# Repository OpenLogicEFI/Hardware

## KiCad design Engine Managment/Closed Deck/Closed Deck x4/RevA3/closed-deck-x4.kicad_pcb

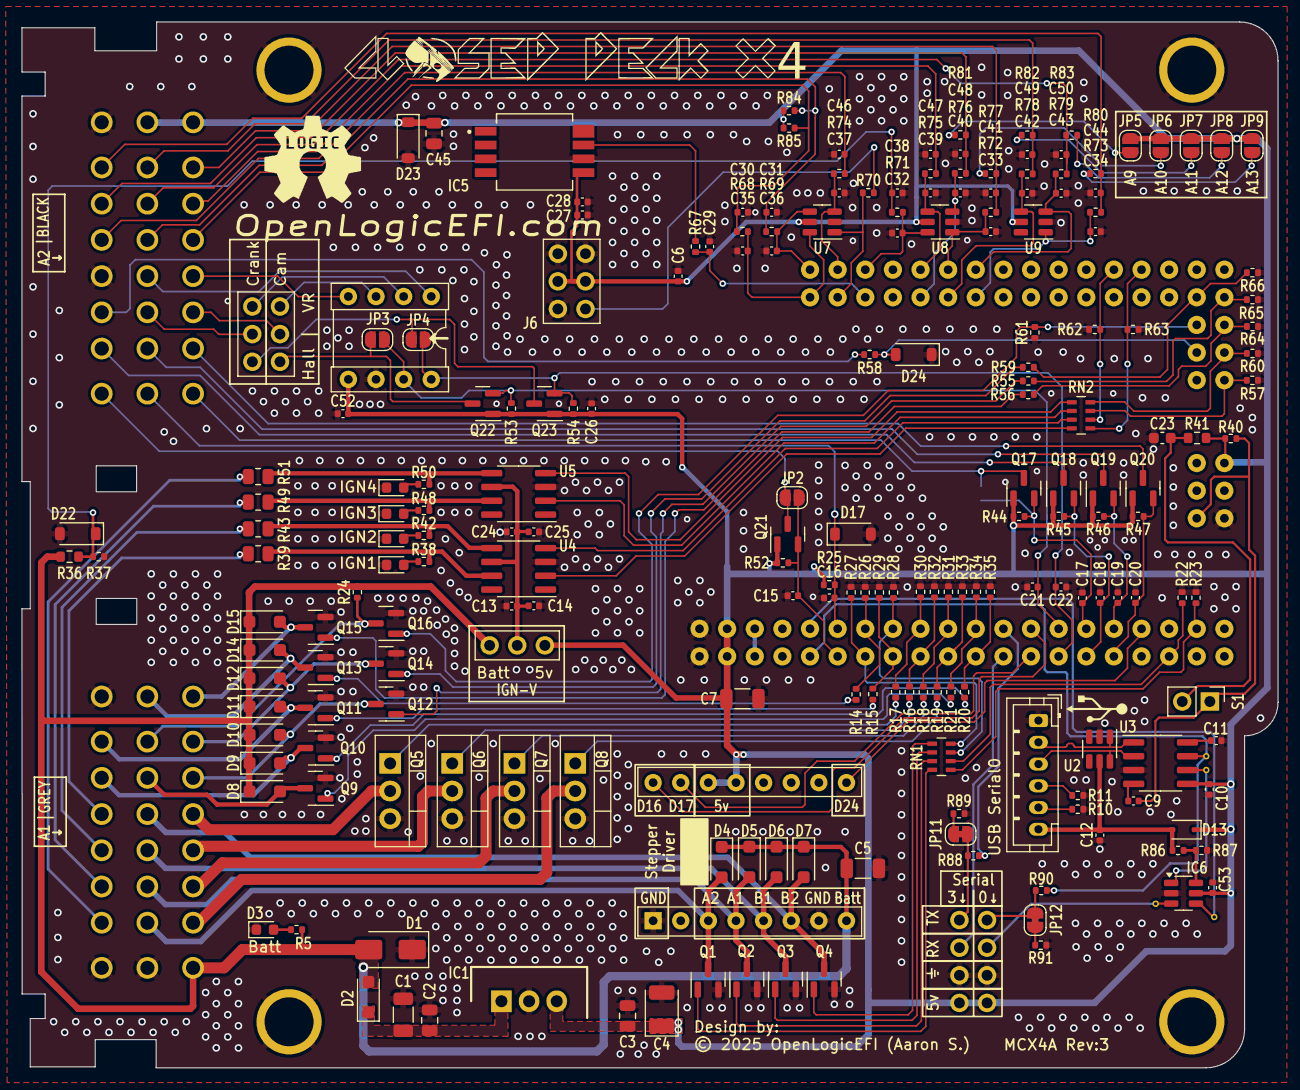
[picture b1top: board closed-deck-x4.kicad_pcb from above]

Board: 2 copper layers, 115.5 x 96.2 mm, 220 parts (1 on the bottom side), 149 nets.

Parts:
A1: GREY; Delphi_Sicma_24_Grey
A2: BLACK; Delphi_Sicma_24_Black
C1, C5, C7: 10uF; C_1206_3216Metric
C2: 330nF; C_0805_2012Metric
C3, C45: 100nF; C_0805_2012Metric
C4: 100uF; CP_EIA-3528-15_AVX-H
C6, C9, C10, C11, C12, C13, C15, C21, C24, C26, C28, C29, C35, C36, C38, C41, C44, C46, C47, C48, C49, C50, C52, C53: 100nF; C_0402_1005Metric
C14, C25, C27: 1u; C_0402_1005Metric
C16, C30, C31, C32, C33, C34, C37, C39, C40, C42, C43: 220nF; C_0402_1005Metric
C17, C18, C19, C20, C22: 10nF; C_0402_1005Metric
C23: 10uF; C_0603_1608Metric
D1: SMAJ18CA; D_SMA
D2, D4, D5, D6, D7, D8, D9, D10, D11, D12, D14, D15: DSK210; D_SOD-123F
D3, D16, D18, D20, D21: LED; LED_0603_1608Metric
D13: 1N5819WS; D_SOD-323
D17, D22, D23, D24: MMSZ5232B; D_SOD-123
H1, H2, H3, H4: MountingHole_Pad; MountingHole_3.5mm_Pad
IC1: 7805; TO-220-SmallHeatSink
IC2: Breakout DRV8825; DVR8825-Labeled-Front
IC5: KP234; KP234-Handsoldering
IC6: 74LVC1G157GV,125; TSOT-23-6
J2: Serial; 2x04-2.54mm-Serial-withSilk
J3: USB-S0; JST_PH_B6B-PH-K_1x06_P2.00mm_Vertical
J4: Input Jumper; PinHeader2x03_Jumper
J5: VR Conditioner; Socket_VRConditioner_Corrected
J6: Map Sensor Socket; PinSocket 2x03
JP1: IGN-V; 1x03-Proto
JP2, JP3, JP4, JP10: FET Bypass; SolderJumper-2_P1.3mm_Open_RoundedPad1.0x1.5mm
JP5, JP6, JP7, JP8, JP9: SolderJumper_2_Open; SolderJumper-2_P1.3mm_Open_RoundedPad1.0x1.5mm
JP11, JP12: Divider Disable; SolderJumper-2_P1.3mm_Bridged_RoundedPad1.0x1.5mm
Q1, Q2, Q3, Q4, Q9, Q10, Q11, Q12, Q13, Q14, Q15, Q16, Q17, Q18, Q19, Q20, Q21, Q22, Q23: AO3400A; SOT-23
Q5, Q6, Q7, Q8: STP75N04Z; TO-220-3_Vertical
R5, R38, R42, R48, R50, R89, R91: 2k; R_0402_1005Metric
R10, R11: 5.1k; R_0402_1005Metric
R14, R15, R20, R21, R55, R56, R59, R68, R69, R70, R71, R72, R73, R74, R75, R76, R78, R79, R86: 470r; R_0402_1005Metric
R16, R17, R18, R19, R37, R44, R45, R46, R47, R52, R53, R54, R58, R88, R90: 1k; R_0402_1005Metric
R22, R23, R26, R27, R28, R29, R34, R35, R64, R65, R66: 100k; R_0402_1005Metric
R24, R40, R87: 10k; R_0402_1005Metric
R25: 2.2k; R_0402_1005Metric
R30, R31, R32, R33, R57, R60, R61, R62, R63: 100K; R_0402_1005Metric
R36: 3.9k; R_0603_1608Metric
R39, R43, R49, R51: 10r; R_0805_2012Metric
R41: 120r; R_0603_1608Metric
R67: 51k; R_0402_1005Metric
R77, R80, R81, R82, R83, R84, R85: 2.49k; R_0402_1005Metric
RN1, RN2: 1k; R_Array_Concave_4x0603
S1: Reset Control; PinHeader_1x02_P2.54mm_Vertical
TP4, TP5, TP8, TP9: TestPoint; TestPoint_THT_D0.6mm_Drill0.3mm
U2, U7, U8, U9: SRV05-4-P-T7; SOT-23-6
U3: CH340N; SOIC-8_3.9x4.9mm_P1.27mm
U4, U5: COS4427; SOIC-8_3.9x4.9mm_P1.27mm
U6: MEGA_PRO_EMBED_CH340G_{slash}_ATMEGA2560; Arduino_Mega_Mini_2560_SmallCrtYd_NoVin

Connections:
+3.3V: U6.3V3_1 (3V3), U6.3V3_2 (3V3)
+5V: A2.A8, A2.B8, C3.1, C4.1, C6.2, C7.1, C10.1, C26.2, C27.1, C28.1, C45.1, C52.2, C53.2, D13.1 (K), D23.1 (K), IC1.3 (OUT), IC2.13 (~RST), IC2.14 (~SLP), IC5.5 (VDD), IC6.5 (VCC), J2.1, J2.2, J5.5, J6.3, J6.4, JP1.3 (B), JP5.1 (A), JP6.1 (A), JP7.1 (A), JP8.1 (A), JP9.1 (A), Q17.1 (G), Q18.1 (G), Q19.1 (G), Q20.1 (G), Q21.1 (G), Q22.1 (G), Q23.1 (G), R25.1, R40.1, R41.2, R44.1, R45.1, R46.1, R47.1, R52.1, R53.1, R54.1, R84.1, R85.1, U3.5 (VCC), U6.5V_1 (5V), U6.5V_2 (5V), U6.5V_3 (5V), U7.5 (REF), U8.5 (REF), U9.5 (REF)
+BATT: A1.A1, C5.1, D1.2 (A2), D2.2 (A), D4.1 (K), D5.1 (K), D6.1 (K), D7.1 (K), D8.1 (K), D9.1 (K), D10.1 (K), D11.1 (K), D12.1 (K), D14.1 (K), D15.1 (K), IC2.8 (VMOT), JP1.1 (A), R5.2, R24.1, R36.2
A9: A2.C6, C48.1, R76.2, R81.2
A10: A2.A7, C41.1, R72.2, R77.2
A11: A2.B7, C49.1, R78.2, R82.2
A12: A2.B6, C50.1, R79.2, R83.2
A13: A2.C7, C44.1, R73.2, R80.2
BOOST: A1.C7, D11.2 (A), Q11.3 (D)
BaroIn: IC5.7 (VOUT), R67.1
CH340-RX0: IC6.1 (I1), TP4.1, U3.6 (RXD)
CLT: A2.A5, C35.1, R68.2, R85.2
Cam2: A2.C1, JP2.1 (A), Q21.3 (D)
Cam-Direct: J4.b3, JP3.1 (A), Q22.3 (D)
Cam-In: A2.A3, J4.b2
Clutch: A2.C3, R58.1
Crank-Direct: J4.a3, JP4.1 (A), Q23.3 (D)
Crank-In: A2.B3, J4.a2
D12-OUT: A1.B6, D8.2 (A), Q9.3 (D)
D13-OUT: A1.C6, D9.2 (A), Q10.3 (D)
D21-IN: A2.C2, Q18.3 (D)
D22-IN: A2.B2, Q19.3 (D)
D23-IN: A2.A2, Q20.3 (D)
D27-OUT: A1.B3, D5.2 (A), IC2.4 (A1), Q2.3 (D)
D28-OUT: A1.B2, D4.2 (A), IC2.3 (A2), Q1.3 (D)
D+: J3.2, U2.1 (I/O_1), U3.1 (UD+)
D-: J3.3, U2.6 (I/O_4), U3.2 (UD-)
Fan: A1.A6, D10.2 (A), Q12.3 (D)
Flex: A2.B1, C16.1, D17.1 (A1), R25.2, U6.D2
Fuel-Pump: A1.A7, D12.2 (A), Q14.3 (D)
GND: A1.B1, A1.C1, A1.C8, A2.C4, A2.C8, C1.2, C2.2, C3.2, C4.2, C5.2, C6.1, C7.2, C10.2, C11.2, C12.2, C13.2, C14.2, C15.1, C16.2, C17.2, C18.2, C19.2, C20.2, C21.1, C22.1, C23.2, C24.2, C25.2, C26.1, C27.2, C28.2, C29.2, C30.2, C31.2, C32.2, C33.2, C34.2, C35.2, C36.2, C37.2, C38.2, C39.2, C40.2, C41.2, C42.2, C43.2, C44.2, C45.2, C46.2, C47.2, C48.2, C49.2, C50.2, C52.1, C53.1, D1.1 (A1), D3.1 (K), D16.1 (K), D17.2 (A2), D18.1 (K), D20.1 (K), D21.1 (K), D22.2 (A2), D23.2 (A), D24.1 (A1), H1.1, H2.1, H3.1, H4.1, IC1.2 (GND), IC2.1 (GND), IC2.7 (GND), IC5.6 (GND), IC6.2 (GND), J2.3, J2.4, J3.1, J5.6, J6.1, J6.5, J6.6, Q1.2 (S), Q2.2 (S), Q3.2 (S), Q4.2 (S), Q5.3 (S), Q6.3 (S), Q7.3 (S), Q8.3 (S), Q9.2 (S), Q10.2 (S), Q11.2 (S), Q12.2 (S), Q13.2 (S), Q14.2 (S), Q15.2 (S), Q16.2 (S), R10.1, R11.2, R22.1, R23.1, R26.1, R27.1, R28.1, R29.1, R30.1, R31.1, R32.1, R33.1, R34.1, R35.1, R37.1, R57.2, R60.2, R61.2, R62.1, R63.2, R64.1, R65.1, R66.1, R87.1, R89.2, R91.2, U2.2 (GND), U3.3 (GND), U4.3 (GND), U5.3 (GND), U6.GND_1 (GND), U6.GND_2 (GND), U6.GND_3 (GND), U7.2 (GND), U8.2 (GND), U9.2 (GND)
IAT: A2.B5, C36.1, R69.2, R84.2
IDLE1: A1.B5, D7.2 (A), IC2.6 (B2), Q4.3 (D)
IDLE2: A1.B4, D6.2 (A), IC2.5 (B1), Q3.3 (D)
IGN1: A1.C5, R39.2
IGN2: A1.C4, R43.2
IGN3: A1.C3, R49.2
IGN4: A1.C2, R51.2
INJ1: A1.A5, Q5.2 (D)
INJ2: A1.A4, Q6.2 (D)
INJ3: A1.A3, Q7.2 (D)
INJ4: A1.A2, Q8.2 (D)
MC-A0: C31.1, R69.1, U6.A0, U7.4 (I/O_3)
MC-A1: C30.1, R68.1, U6.A1, U7.6 (I/O_4)
MC-A2: C37.1, R74.1, U6.A2, U7.3 (I/O_2)
MC-A3: R70.1, U6.A3, U7.1 (I/O_1)
MC-A4: C32.1, R71.1, U6.A4, U8.6 (I/O_4)
MC-A5: C29.1, R67.2, U6.A5
MC-A8: C39.1, R75.1, U6.A8, U8.4 (I/O_3)
MC-A9: C40.1, R76.1, U6.A9, U8.3 (I/O_2)
MC-A10: C33.1, R72.1, U6.A10, U8.1 (I/O_1)
MC-A11: C42.1, R78.1, U6.A11, U9.4 (I/O_3)
MC-A12: C43.1, R79.1, U6.A12, U9.3 (I/O_2)
MC-A13: C34.1, R73.1, U6.A13, U9.1 (I/O_1)
MC-D0-RX0: IC6.4 (Y), TP8.1, U6.RX
MC-D1-TX0: R90.1, TP5.1, U3.7 (TXD), U6.TX
MC-D3: C15.2, JP2.2 (B), Q21.2 (S), R52.2, U6.D3
MC-D4: R14.1, R26.2, U6.D4
MC-D5: R27.2, RN1.8 (R1.2), U6.D5
MC-D6: R28.2, RN1.7 (R2.2), U6.D6
MC-D7: R15.1, R29.2, U6.D7
MC-D8: R17.1, R30.2, U6.D8
MC-D9: R16.1, R32.2, U6.D9
MC-D10: R18.1, R31.2, U6.D10
MC-D11: R19.1, R33.2, U6.D11
MC-D12: R21.1, R34.2, U6.D12
MC-D13: R20.1, R35.2, U6.D13
MC-D14-TX3: R88.1, U6.D14
MC-D15-RX3: J2.5, U6.D15
MC-D16: IC2.16 (DIR), U6.D16
MC-D17: IC2.15 (STEP), U6.D17
MC-D18: C21.2, J5.7, JP3.2 (B), Q22.2 (S), R53.2, U6.D18
MC-D19: C22.2, J5.8, JP4.2 (B), Q23.2 (S), R54.2, U6.D19
MC-D20: C17.1, JP10.2 (B), Q17.2 (S), R44.2, U6.D20
MC-D21: C18.1, Q18.2 (S), R45.2, U6.D21
MC-D22: C19.1, Q19.2 (S), R46.2, U6.D22
MC-D23: C20.1, Q20.2 (S), R47.2, U6.D23
MC-D24: IC2.9 (~EN), U6.D24
MC-D27: R22.2, RN1.6 (R3.2), U6.D27
MC-D28: R23.2, RN1.5 (R4.2), U6.D28
MC-D38: R62.2, RN2.6 (R3.2), U6.D38
MC-D40: R63.1, RN2.5 (R4.2), U6.D40
MC-D45: R59.1, R66.2, U6.D45
MC-D47: R55.1, R65.2, U6.D47
MC-D48: R56.1, R64.2, U6.D48
MC-D49: Q16.1 (G), R61.1, U6.D49
MC-D50: R60.1, RN2.8 (R1.2), U6.D50
MC-D51: D24.2 (A2), R58.2, U6.D51
MC-D52: R57.1, RN2.7 (R2.2), U6.D52
MC-RESET: C9.2, R40.2, S1.1, U6.RESET
MapIn: J6.2, R70.2
unnamed: C1.1, C2.1, D2.1 (K), IC1.1 (IN)
unnamed: D3.2 (A), R5.1
unnamed: D16.2 (A), R38.1
unnamed: D18.2 (A), R42.1
unnamed: D20.2 (A), R48.1
unnamed: D21.2 (A), R50.1
unnamed: C38.1, D22.1 (A1), R36.1, R37.2, R71.2
unnamed: IC6.6 (S), R86.1, R87.2
unnamed: J2.7, JP11.2 (B), R88.2
unnamed: J2.8, JP12.1 (A), R90.2
unnamed: J3.4, R11.1
unnamed: J3.5, R10.2
unnamed: C13.1, C14.1, C24.1, C25.1, JP1.2 (C), U4.6 (V+), U5.6 (V+)
unnamed: JP5.2 (B), R81.1
unnamed: JP6.2 (B), R77.1
unnamed: JP7.2 (B), R82.1
unnamed: JP8.2 (B), R83.1
unnamed: JP9.2 (B), R80.1
unnamed: JP11.1 (A), R89.1
unnamed: JP12.2 (B), R91.1
unnamed: Q1.1 (G), RN1.4 (R4.1)
unnamed: Q2.1 (G), RN1.3 (R3.1)
unnamed: Q3.1 (G), RN1.2 (R2.1)
unnamed: Q4.1 (G), RN1.1 (R1.1)
unnamed: Q5.1 (G), R17.2
unnamed: Q6.1 (G), R16.2
unnamed: Q7.1 (G), R18.2
unnamed: Q8.1 (G), R19.2
unnamed: Q9.1 (G), R21.2
unnamed: Q10.1 (G), R20.2
unnamed: Q11.1 (G), R15.2
unnamed: Q12.1 (G), R55.2
unnamed: Q13.1 (G), R14.2
unnamed: Q14.1 (G), R59.2
unnamed: Q15.1 (G), R56.2
unnamed: RN2.1 (R1.1), U5.4 (IN_B)
unnamed: RN2.2 (R2.1), U5.2 (IN_A)
unnamed: RN2.3 (R3.1), U4.4 (IN_B)
unnamed: RN2.4 (R4.1), U4.2 (IN_A)
unnamed: C23.1, R41.1, S1.2
unnamed: C11.1, U3.8 (V3)
unnamed: C9.1, U3.4 (~RTS)
unnamed: R38.2, R39.1, U4.7 (OUT_A)
unnamed: R42.2, R43.1, U4.5 (OUT_B)
unnamed: R48.2, R49.1, U5.7 (OUT_A)
unnamed: R50.2, R51.1, U5.5 (OUT_B)
O2: A2.A6, C47.1, R75.2
Proto-RX0: IC6.3 (I0), J2.6, TP9.1
TPS: A2.C5, C46.1, R74.2
Tach: A1.B7, Q16.3 (D), R24.2
VBus: C12.1, D13.2 (A), J3.6, R86.2, U2.5 (REF)
VR1+: J4.a1, J5.2
VR1-: A2.B4, J5.1
VR2+: J4.b1, J5.3
VR2-: A2.A4, J5.4
VSS-IN: A2.A1, JP10.1 (A), Q17.3 (D)
VVT: A1.B8, D14.2 (A), Q13.3 (D)
VVT2: A1.A8, D15.2 (A), Q15.3 (D)

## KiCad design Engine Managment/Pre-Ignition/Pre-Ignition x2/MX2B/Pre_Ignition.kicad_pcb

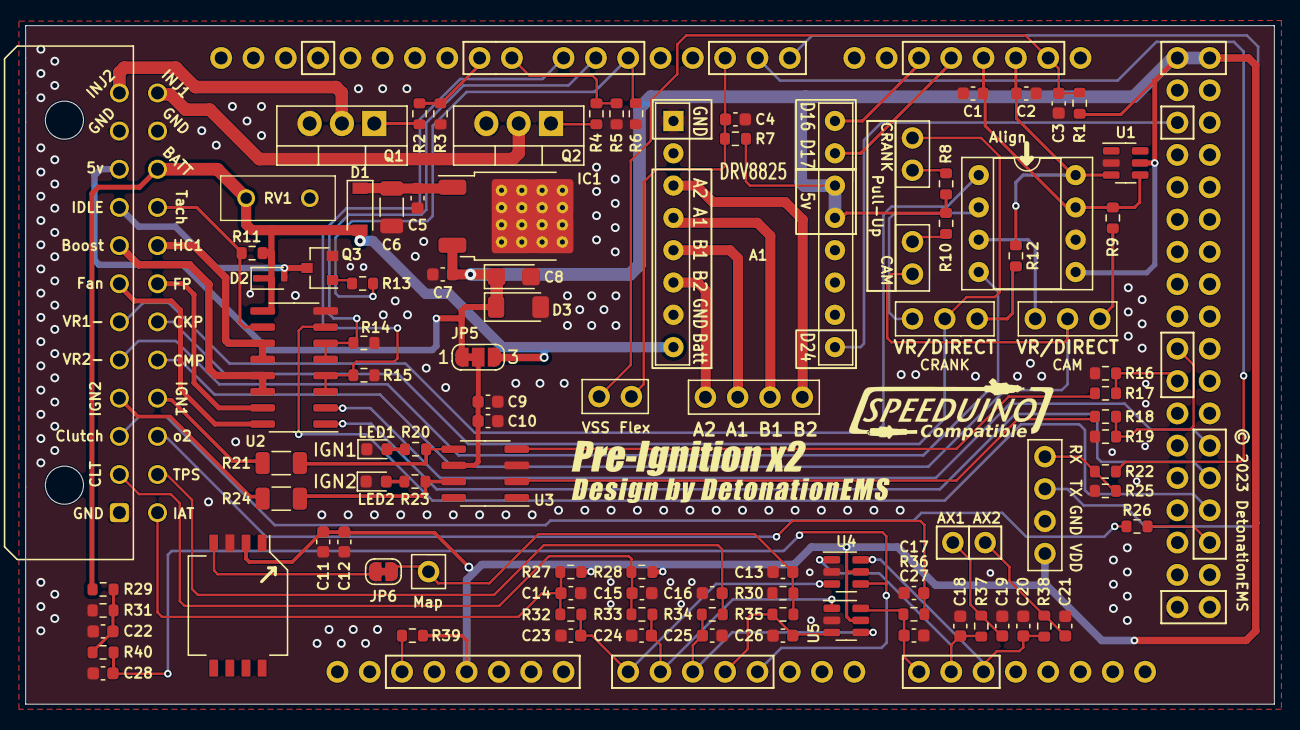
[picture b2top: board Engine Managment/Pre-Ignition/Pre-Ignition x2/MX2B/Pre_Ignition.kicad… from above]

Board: 2 copper layers, 98.2 x 53.3 mm, 102 parts (0 on the bottom side), 78 nets.

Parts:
A1: Pololu_Breakout_DRV8825; DVR8825-Labeled-Front
C1, C3, C7, C10, C12, C14, C15, C16, C17, C19, C21, C22: 100nF; C_0603_1608Metric
C2: 10nF; C_0603_1608Metric
C4, C18, C20, C23, C24, C25, C27, C28: 220nF; C_0603_1608Metric
C5: 2.2uF; C_0603_1608Metric
C6: 330nF; C_1206_3216Metric
C8: 10uF; CP_EIA-3216-18_Kemet-A
C9, C11: 1uF; C_0603_1608Metric
C13: 47pF; C_0603_1608Metric
C26: 330nF; C_0603_1608Metric
D1: B5819; D_SOD-123
D2: 1N4148WS; D_SOD-323F
D3: ZMM5V6-M; D_MiniMELF
G1: Logo_Open_Hardware_Small; SpeeduinoCompatible-17mm
G2: Logo_Open_Hardware_Small; Pre-Ignition-800
G3: LOGO; Design by 25mm
IC1: L78M05ABDT-TR; TO-252-2-Thermal
IC2: MPXH6400; MPXH6250
J1: VR_Header; DIP-8_W7.62mm_Socket_VRConditioner
J2, J5: Conn_01x04; 1x02-Proto
J3, J6: Conn_01x04; 1X4-PROTO
J4: Conn_02x12_Counter_Clockwise; Molex_Micro-Fit_3.0_43045-2400_2x12_P3.00mm_Horizontal
J7: Conn_01x04; 1x1-GPIO
JP1, JP2: Pullup; 1x02-Proto
JP3: VR-HALL; 3x1-GPIO
JP4: VR-Hall; 3x1-GPIO
JP5: Jumper_3_Bridged12; SolderJumper-3_P1.3mm_Bridged12_RoundedPad1.0x1.5mm_NumberL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
JP6: SolderJumper-2_P1.3mm_Bridged_RoundedPad1.0x1.5mm
LED1, LED2: LED; LED_0603_1608Metric
Q1, Q2: STP62NS04Z; TO-220-3_Vertical
Q3: AO3400A; SOT-23
R1, R2, R4, R8, R10, R17, R18, R22, R26, R31: 1K; R_0603_1608Metric
R3, R5, R6, R14, R15, R16, R19: 100K; R_0603_1608Metric
R7, R20, R23: 2.4k; R_0603_1608Metric
R9, R12, R32, R33, R34, R35, R36, R37, R38, R40: 470; R_0603_1608Metric
R11, R39: 10k; R_0603_1608Metric
R13: 120; R_0603_1608Metric
R21, R24: 10; R_1206_3216Metric
R25: 2K; R_0603_1608Metric
R27, R28: 2.49k; R_0603_1608Metric
R29: 3.9k; R_0603_1608Metric
R30: 51k; R_0603_1608Metric
RV1: MOV; MOV07D220KTR
U1, U4, U5: SRV05-4-P-T7; SOT-23-6
U2: ULN2003A; SOIC-16_3.9x9.9mm_P1.27mm
U3: TC4427; SOIC-8_3.9x4.9mm_P1.27mm
XA1: Arduino_Mega2560_Shield-Arduino; Arduino_Mega2560_Shield_IO_Only_No_Silk_Screen

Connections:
+5V: A1.13 (~RST), A1.14 (~SLP), C7.1, C8.1, C11.2, C12.1, D3.1 (K), IC1.3 (OUT), IC2.2 (VS), J1.5, J4.10, J6.1, JP5.1 (A), R1.1, R7.1, R8.2, R10.2, R27.2, R28.2, R39.2, U1.5 (REF), U4.5 (REF), U5.5 (REF), XA1.5V1 (5V), XA1.5V3 (5V), XA1.5V4 (5V)
+BATT: A1.8 (VMOT), D1.2 (A), D2.1 (K), J4.22, JP5.3 (B), R11.2, R29.2, RV1.1, U2.9 (COM)
A-IN1: C19.1, J5.2, R37.2
A-IN2: C21.1, J5.1, R38.2
BOOST: J4.8, U2.13 (O4), U2.14 (O3)
CLT: C15.1, J4.2, R28.1, R33.2
Cam-In: J4.17, JP2.2, JP4.2
Clutch: J4.3, R26.2
Crank-In: J4.18, JP1.1, JP3.2
Fan: J4.7, U2.16 (O1)
Flex: C4.1, J2.2, R7.2, XA1.D2 (D2_INT0)
Fuel-Pump: J4.19, U2.15 (O2)
GND: A1.1 (GND), A1.7 (GND), C1.1, C2.1, C3.2, C4.2, C5.2, C6.1, C7.2, C8.2, C9.2, C10.2, C11.1, C12.2, C13.2, C14.2, C15.2, C16.2, C17.2, C18.2, C19.2, C20.2, C21.2, C22.2, C23.2, C24.2, C25.2, C26.1, C27.2, C28.2, D3.2 (A), IC1.2 (GND), IC2.3 (GND), J1.6, J4.1, J4.11, J4.23, J6.2, LED1.1 (K), LED2.1 (K), Q1.3 (S), Q2.3 (S), Q3.2 (S), R3.2, R5.1, R6.1, R14.2, R15.1, R16.1, R19.2, R25.1, R30.2, R31.1, RV1.2, U1.2 (GND), U2.8 (GND), U3.3 (GND), U4.2 (GND), U5.2 (GND), XA1.GND1 (GND), XA1.GND2 (GND), XA1.GND3 (GND), XA1.GND5 (GND), XA1.GND6 (GND)
HC1: J4.20, U2.11 (O6), U2.12 (O5)
IAT: C14.1, J4.13, R27.1, R32.2
IDLE: D2.2 (A), J4.9, Q3.3 (D)
IGN1: J4.16, R21.1
IGN2: J4.4, R24.1
IGN-V: C9.1, C10.1, JP5.2 (C), U3.6 (V+)
INJ1: J4.24, Q2.2 (D)
INJ2: J4.12, Q1.2 (D)
MC-A0: C23.1, R32.1, U4.3 (I/O_2), XA1.A0
MC-A1: C24.1, R33.1, U5.1 (I/O_1), XA1.A1
MC-A2: C25.1, R34.1, U5.4 (I/O_3), XA1.A2
MC-A3: C26.2, R35.2, U5.3 (I/O_2), XA1.A3
MC-A4: C28.1, R40.1, U4.4 (I/O_3), XA1.A4
MC-A8: C27.1, R36.1, U5.6 (I/O_4), XA1.A8
MC-A9: C18.1, R37.1, U4.1 (I/O_1), XA1.A9
MC-A10: C20.1, R38.1, U4.6 (I/O_4), XA1.A10
MC-D0: J6.3, XA1.D0 (D0_RX0)
MC-D1: R22.2, XA1.D1 (D1_TX0)
MC-D5: R6.2, R13.1, XA1.D5
MC-D6: R14.1, U2.5 (I5), U2.6 (I6), XA1.D6
MC-D7: R15.2, U2.3 (I3), U2.4 (I4), XA1.D7
MC-D8: R4.2, R5.2, XA1.D8
MC-D9: R2.2, R3.1, XA1.D9
MC-D16: A1.16 (DIR), XA1.D16 (D16_TX2)
MC-D17: A1.15 (STEP), XA1.D17 (D17_RX2)
MC-D18: C1.2, J1.7, R9.1, U1.4 (I/O_3), XA1.D18 (D18_TX1)
MC-D19: C2.2, J1.8, R12.1, U1.3 (I/O_2), XA1.D19 (D19_RX1)
MC-D20: C3.1, J2.1, R1.2, XA1.D20 (D20_SDA)
MC-D24: A1.9 (~EN), XA1.D24
MC-D38: R18.2, R19.1, XA1.D38
MC-D40: R16.2, R17.2, XA1.D40
MC-D45: U2.2 (I2), XA1.D45
MC-D47: U2.1 (I1), XA1.D47
MC-D49: U2.7 (I7), XA1.D49
MC-D51: R26.1, XA1.D51
MC-RESET: R39.1, XA1.RST1 (RESET)
Map-External: C13.1, J7.1, JP6.1 (A), R30.1, R35.1
unnamed: C22.1, R29.1, R31.2, R40.2
unnamed: C5.1, C6.2, D1.1 (K), IC1.1 (IN)
unnamed: IC2.4 (VOUT), JP6.2 (B)
unnamed: J1.2, JP3.3
unnamed: J1.3, JP4.1
unnamed: J6.4, R22.1, R25.2
unnamed: JP1.2, R8.1
unnamed: JP2.1, R10.1
unnamed: JP3.1, R12.2
unnamed: JP4.3, R9.2
unnamed: LED1.2 (A), R20.1
unnamed: LED2.2 (A), R23.2
unnamed: Q1.1 (G), R2.1
unnamed: Q2.1 (G), R4.1
unnamed: Q3.1 (G), R13.2
unnamed: R18.1, U3.2 (IN_A)
unnamed: R17.1, U3.4 (IN_B)
unnamed: R23.1, R24.2, U3.7 (OUT_A)
unnamed: R20.2, R21.2, U3.5 (OUT_B)
O2: C17.1, J4.15, R36.2
Step-A1: A1.4 (A1), J3.2
Step-A2: A1.3 (A2), J3.1
Step-B1: A1.5 (B1), J3.3
Step-B2: A1.6 (B2), J3.4
TPS: C16.1, J4.14, R34.2
Tach: J4.21, R11.1, U2.10 (O7)
VR1-: J1.1, J4.6
VR2-: J1.4, J4.5

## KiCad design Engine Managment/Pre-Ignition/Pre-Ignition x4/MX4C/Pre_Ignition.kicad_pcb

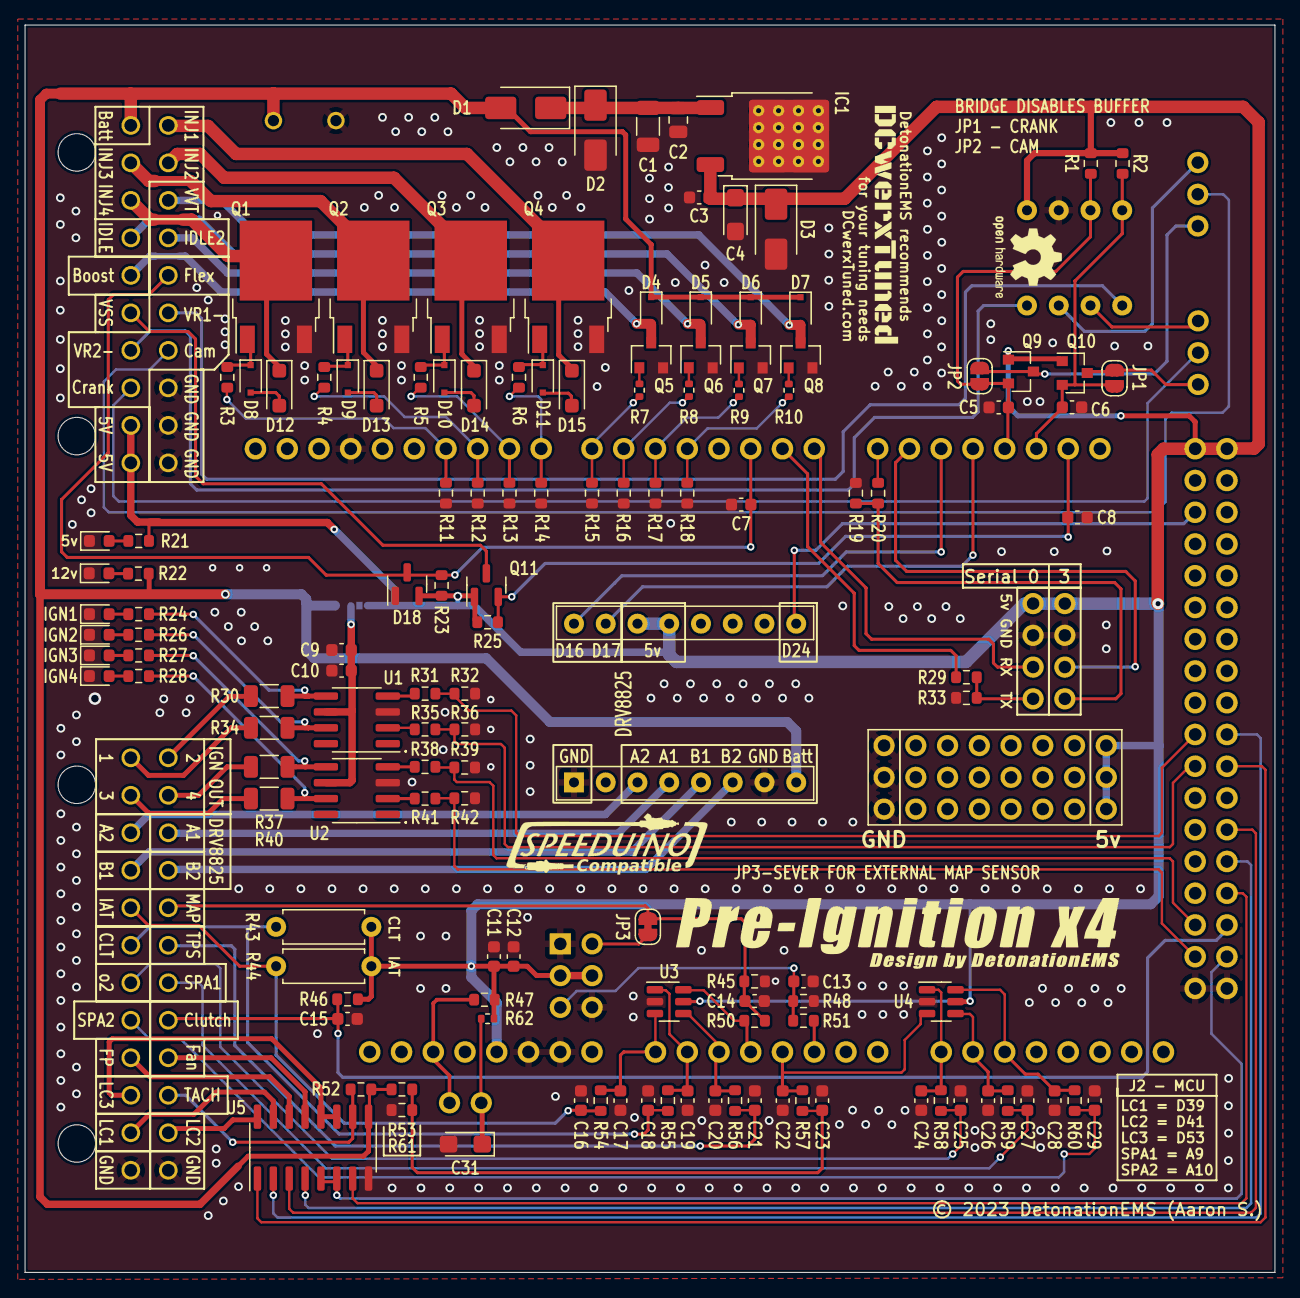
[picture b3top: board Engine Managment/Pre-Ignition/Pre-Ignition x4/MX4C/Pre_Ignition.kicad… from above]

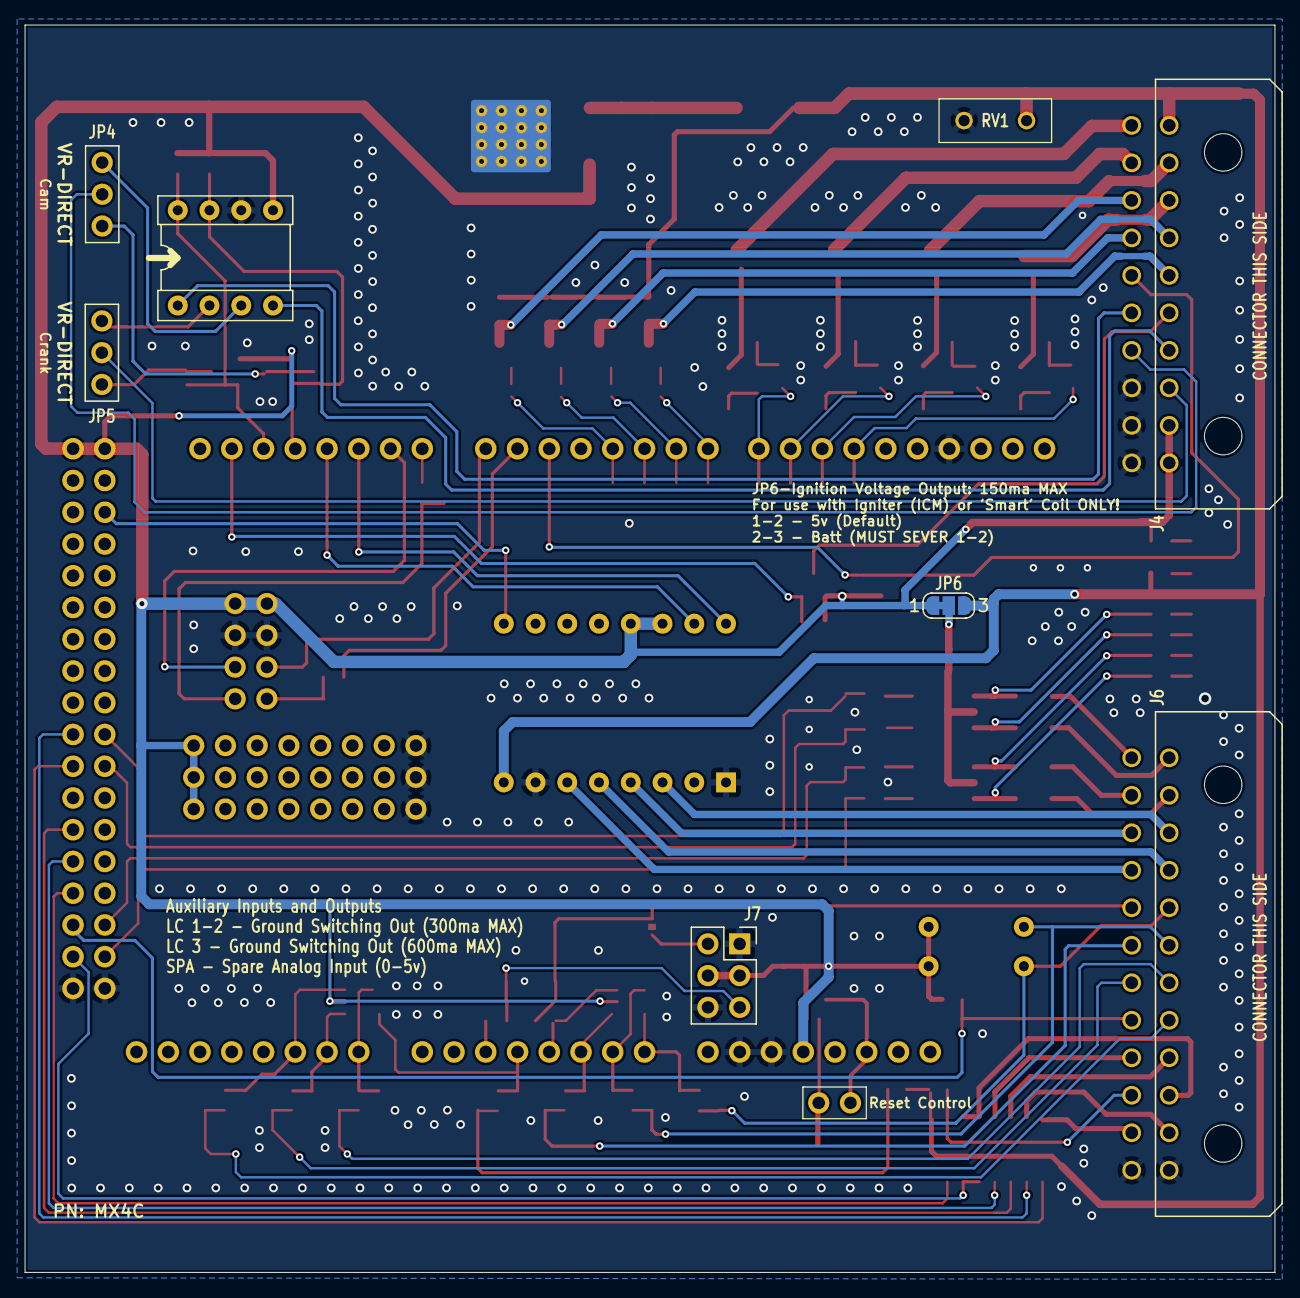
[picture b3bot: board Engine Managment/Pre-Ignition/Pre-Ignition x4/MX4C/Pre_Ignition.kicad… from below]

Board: 2 copper layers, 100.0 x 99.8 mm, 152 parts (9 on the bottom side), 115 nets.

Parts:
A1: DRV8825; DVR8825-Labeled-Front
C1: 2.2uF; C_1206_3216Metric
C2: 330nF; C_0805_2012Metric
C3, C5, C9, C12, C16, C18, C21, C23, C25, C27, C29: 100nF; C_0603_1608Metric
C4, C31: 10uF; CP_EIA-3216-18_Kemet-A
C6, C8: 10nF; C_0603_1608Metric
C7, C15, C17, C19, C20, C22, C24, C26, C28: 220nF; C_0603_1608Metric
C10, C11: 1uF; C_0603_1608Metric
C13, C14: 47pF; C_0603_1608Metric
D1: M7; D_SMA
D2: TVS 26a; D_SMA
D3: TVS 5.0A; D_SMA
D4, D5, D6, D7, D8, D9, D10, D11: 1N4148WS; D_SOD-323F
D12, D13, D14, D15: SMF30CA; D_SOD-123F
D16, D17: LED-Green; LED_0603_1608Metric
D18: BAV99; SOT-23
G1: DCWERX; DCWerx-19mm
G2: OSHW-Logo2_7.3x6mm_SilkScreen
G3: LOGO; SpeeduinoCompatible-17mm
G4: Pre-Ignition; Pre-IgnitionX4-35mm
G5: DESIGN; Design by 20mm
IC1: L78M05ABDT-TR; TO-252-2-Thermal
IGN1, IGN2, IGN3, IGN4: LED-Green; LED_0603_1608Metric
J1: Serial0; 1X4-PROTO
J2: Serial3; 1X4-PROTO
J3: Conn_02x12_Counter_Clockwise; PROTO-3X8-24pin
J4: Conn_02x10_Counter_Clockwise; Molex_Micro-Fit_3.0_43045-2000_2x10_P3.00mm_Horizontal
J5: VR_Header; Socket_VRConditioner_Corrected
J6: Conn_02x12_Counter_Clockwise; Molex_Micro-Fit_3.0_43045-2400_2x12_P3.00mm_Horizontal
J7: Map/Baro Sensor Socket; PinSocket_2x03_P2.54mm_Vertical
J8: Reset Control; 1x02-Proto
JP1, JP2: MOS Bypass; SolderJumper-2_P1.3mm_Open_RoundedPad1.0x1.5mm
JP3: MAP bypass; SolderJumper-2_P1.3mm_Bridged_RoundedPad1.0x1.5mm
JP4, JP5: Conn_01x03; 1x03-Proto
JP6: SolderJumper_3_Bridged12; SolderJumper-3_P1.3mm_Bridged12_RoundedPad1.0x1.5mm_NumberL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
Q1, Q2, Q3, Q4: IRFR024; TO-252-2
Q5, Q6, Q7, Q8, Q9, Q10, Q11: AO3400A; SOT-23
R1, R2, R3, R4, R5, R6, R20, R21, R25, R29, R31, R35, R38, R41, R46, R61: 1k; R_0603_1608Metric
R7, R8, R9, R10, R62: 470r; R_0402_1005Metric
R11, R12, R13, R14, R15, R16, R17, R18, R32, R36, R39, R42: 100k; R_0603_1608Metric
R19, R33: 2k; R_0603_1608Metric
R22, R23, R24, R26, R27, R28: 2.4k; R_0603_1608Metric
R30, R34, R37, R40: 10; R_1206_3216Metric
R43, R44: 2.49k; R_Axial_DIN0207_L6.3mm_D2.5mm_P7.62mm_Horizontal
R45, R48: 51k; R_0603_1608Metric
R47, R52: 10k; R_0603_1608Metric
R50, R51, R54, R55, R56, R57, R58, R59, R60: 470; R_0603_1608Metric
R53: 3.9k; R_0603_1608Metric
RV1: 7D220KTR; MOV07D220KTR
U1, U2: TC4424; SOIC-8_3.9x4.9mm_P1.27mm
U3, U4: SRV05-4-P-T7; SOT-23-6
U5: ULN2003A; SOIC-16_3.9x9.9mm_P1.27mm
XA1: Arduino_Mega2560_Shield-Arduino; Arduino-Mega2560-Shield-Speeduino

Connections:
+5V: A1.13 (~RST), A1.14 (~SLP), C3.2, C4.1, C11.2, C12.2, D3.1 (A1), D18.2 (A), IC1.3 (OUT), J1.1, J2.1, J3.22, J3.23, J3.24, J4.9, J4.10, J5.5, J7.3, J7.4, JP6.1 (A), Q9.1 (G), Q10.1 (G), Q11.1 (G), R1.1, R2.1, R21.1, R23.1, R25.1, R43.2, R44.2, R46.1, R47.1, R62.2, U3.5 (REF), U4.5 (REF), XA1.5V1 (5V), XA1.5V3 (5V), XA1.5V4 (5V)
+BATT: A1.8 (VMOT), D1.2 (A), D4.1 (K), D5.1 (K), D6.1 (K), D7.1 (K), J4.1, JP6.3 (B), R22.2, R52.2, R53.2, RV1.1, U5.9 (COM)
/Inputs/Net-(JP1-A): JP1.1 (A), JP5.1, Q10.3 (D)
/Inputs/Net-(JP2-A): JP2.1 (A), JP4.1, Q9.3 (D)
A9: C27.1, J6.19, R59.2
A10: C29.1, J6.8, R60.2
BOOST: D4.2 (A), J4.5, Q5.3 (D)
BaroIn: C13.1, J7.5, R48.1, R51.1
CLT: C18.1, J6.6, R43.1, R55.2
Cam-In: J4.17, JP4.2
Cam-VR: J5.3, JP4.3
Clutch: C15.1, J6.20, R46.2, XA1.D51
Crank-In: J4.8, JP5.2
Crank-VR: J5.2, JP5.3
D39: J6.11, U5.15 (O2)
D41: J6.23, U5.16 (O1)
D53: J6.10, U5.11 (O6), U5.12 (O5)
Fan: J6.21, U5.13 (O4)
Flex: C7.1, D18.3 (K), J4.15, R23.2, XA1.D2 (D2_INT0)
Fuel-Pump: J6.9, U5.14 (O3)
GND: A1.1 (GND), A1.7 (GND), C1.2, C2.2, C3.1, C4.2, C5.1, C6.1, C7.2, C8.2, C9.2, C10.2, C11.1, C12.1, C13.2, C14.2, C15.2, C16.2, C17.2, C18.2, C19.2, C20.2, C21.2, C22.2, C23.2, C24.2, C25.2, C26.2, C27.2, C28.2, C29.2, C31.2, D2.2 (A2), D3.2 (A2), D16.1 (K), D17.1 (K), D18.1 (K), IC1.2 (GND), IGN1.1 (K), IGN2.1 (K), IGN3.1 (K), IGN4.1 (K), J1.2, J2.2, J3.1, J3.2, J3.3, J4.18, J4.19, J4.20, J5.6, J6.12, J6.24, J7.1, J7.6, Q1.3 (S), Q2.3 (S), Q3.3 (S), Q4.3 (S), Q5.2 (S), Q6.2 (S), Q7.2 (S), Q8.2 (S), R11.1, R12.1, R13.1, R14.1, R15.1, R16.1, R17.1, R18.1, R19.1, R32.1, R33.1, R36.2, R39.1, R42.2, R45.1, R48.2, R61.1, RV1.2, U1.3 (GND), U2.3 (GND), U3.2 (GND), U4.2 (GND), U5.8 (GND), XA1.GND1 (GND), XA1.GND2 (GND), XA1.GND3 (GND), XA1.GND5 (GND), XA1.GND6 (GND)
IAT: C16.1, J6.5, R44.1, R54.2
IDLE: D6.2 (A), J4.4, Q7.3 (D)
IDLE2: D5.2 (A), J4.14, Q6.3 (D)
IGN1: J6.1, R34.1
IGN2: J6.13, R30.1
IGN3: J6.2, R40.1
IGN4: J6.14, R37.1
IGN-PWR: C9.1, C10.1, JP6.2 (C), U1.6 (V+), U2.6 (V+)
INJ1: D15.1 (A1), J4.11, Q4.2 (D)
INJ2: D14.1 (A1), J4.12, Q3.2 (D)
INJ3: D13.1 (A1), J4.2, Q2.2 (D)
INJ4: D12.1 (A1), J4.3, Q1.2 (D)
MC-A0: C17.1, R54.1, U3.3 (I/O_2), XA1.A0
MC-A1: C19.1, R55.1, U3.1 (I/O_1), XA1.A1
MC-A2: C20.1, R56.1, U3.4 (I/O_3), XA1.A2
MC-A3: R50.2, U3.6 (I/O_4), XA1.A3
MC-A4: C22.1, R57.1, U4.3 (I/O_2), XA1.A4
MC-A5: R51.2, XA1.A5
MC-A8: C24.1, R58.1, U4.1 (I/O_1), XA1.A8
MC-A9: C26.1, R59.1, U4.4 (I/O_3), XA1.A9
MC-A10: C28.1, R60.1, U4.6 (I/O_4), XA1.A10
MC-D0-RX: J1.3, XA1.D0 (D0_RX0)
MC-D1-TX: R29.2, XA1.D1 (D1_TX0)
MC-D4: R10.2, R18.2, XA1.D4
MC-D5: R9.2, R17.2, XA1.D5
MC-D6: R8.2, R16.2, XA1.D6
MC-D7: R7.2, R15.2, XA1.D7
MC-D8: R6.2, R14.2, XA1.D8
MC-D9: R5.2, R13.2, XA1.D9
MC-D10: R4.2, R12.2, XA1.D10
MC-D11: R3.2, R11.2, XA1.D11
MC-D14-TX: R20.2, XA1.D14 (D14_TX3)
MC-D15-RX: J2.3, XA1.D15 (D15_RX3)
MC-D16: A1.16 (DIR), XA1.D16 (D16_TX2)
MC-D17: A1.15 (STEP), XA1.D17 (D17_RX2)
MC-D18: C5.2, J5.7, JP2.2 (B), Q9.2 (S), R1.2, XA1.D18 (D18_TX1)
MC-D19: C6.2, J5.8, JP1.2 (B), Q10.2 (S), R2.2, XA1.D19 (D19_RX1)
MC-D20: C8.1, Q11.2 (S), R25.2, XA1.D20 (D20_SDA)
MC-D24: A1.9 (~EN), XA1.D24
MC-D38: R31.2, R32.2, XA1.D38
MC-D39: U5.2 (I2), XA1.D39
MC-D40: R35.2, R36.1, XA1.D40
MC-D41: U5.1 (I1), XA1.D41
MC-D45: U5.3 (I3), XA1.D45
MC-D47: U5.4 (I4), XA1.D47
MC-D49: U5.7 (I7), XA1.D49
MC-D50: R38.2, R39.2, XA1.D50
MC-D52: R41.2, R42.1, XA1.D52
MC-D53: U5.5 (I5), U5.6 (I6), XA1.D53 (D53_SS)
MC-RESET: J8.1, R47.2, XA1.RST1 (RESET)
Map-External: C14.1, J6.17, JP3.1 (A), R45.2, R50.1
MapIn: J7.2, JP3.2 (B)
unnamed: C23.1, R53.1, R57.2, R61.2
unnamed: C1.1, C2.1, D1.1 (K), D2.1 (A1), IC1.1 (IN)
unnamed: D8.1 (K), Q1.1 (G), R3.1
unnamed: D9.1 (K), Q2.1 (G), R4.1
unnamed: D10.2 (A), D14.2 (A2)
unnamed: D10.1 (K), Q3.1 (G), R5.1
unnamed: D11.2 (A), D15.2 (A2)
unnamed: D11.1 (K), Q4.1 (G), R6.1
unnamed: D8.2 (A), D12.2 (A2)
unnamed: D9.2 (A), D13.2 (A2)
unnamed: D16.2 (A), R21.2
unnamed: D17.2 (A), R22.1
unnamed: IGN1.2 (A), R24.1
unnamed: IGN2.2 (A), R26.2
unnamed: IGN3.2 (A), R27.1
unnamed: IGN4.2 (A), R28.2
unnamed: J1.4, R29.1, R33.2
unnamed: J2.4, R19.2, R20.1
unnamed: C31.1, J8.2, R62.1
unnamed: Q5.1 (G), R7.1
unnamed: Q6.1 (G), R8.1
unnamed: Q7.1 (G), R9.1
unnamed: Q8.1 (G), R10.1
unnamed: R35.1, U1.2 (IN_A)
unnamed: R31.1, U1.4 (IN_B)
unnamed: R26.1, R34.2, U1.7 (OUT_A)
unnamed: R24.2, R30.2, U1.5 (OUT_B)
unnamed: R41.1, U2.2 (IN_A)
unnamed: R38.1, U2.4 (IN_B)
unnamed: R28.1, R40.2, U2.7 (OUT_A)
unnamed: R27.2, R37.2, U2.5 (OUT_B)
O2: C25.1, J6.7, R58.2
Step-A1: A1.4 (A1), J6.15
Step-A2: A1.3 (A2), J6.3
Step-B1: A1.5 (B1), J6.4
Step-B2: A1.6 (B2), J6.16
TPS: C21.1, J6.18, R56.2
Tach: J6.22, R52.1, U5.10 (O7)
VR1-: J4.16, J5.1
VR2-: J4.7, J5.4
VSS: J4.6, Q11.3 (D)
VVT: D7.2 (A), J4.13, Q8.3 (D)

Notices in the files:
Engine Managment/Closed Deck/Closed Deck x4/RevA3/closed-deck-x4.kicad_pcb:
© 2025 OpenLogicEFI (Aaron S.)
Engine Managment/Pre-Ignition/Pre-Ignition x2/MX2B/Pre_Ignition.kicad_pcb:
© 2023 DetonationEMS
Engine Managment/Pre-Ignition/Pre-Ignition x4/MX4C/Pre_Ignition.kicad_pcb:
© 2023 DetonationEMS (Aaron S.)
Engine Simulation/8 Channel/RevB/Simulator.kicad_pcb:
DetonationEMS © 2023 (Aaron S.)
